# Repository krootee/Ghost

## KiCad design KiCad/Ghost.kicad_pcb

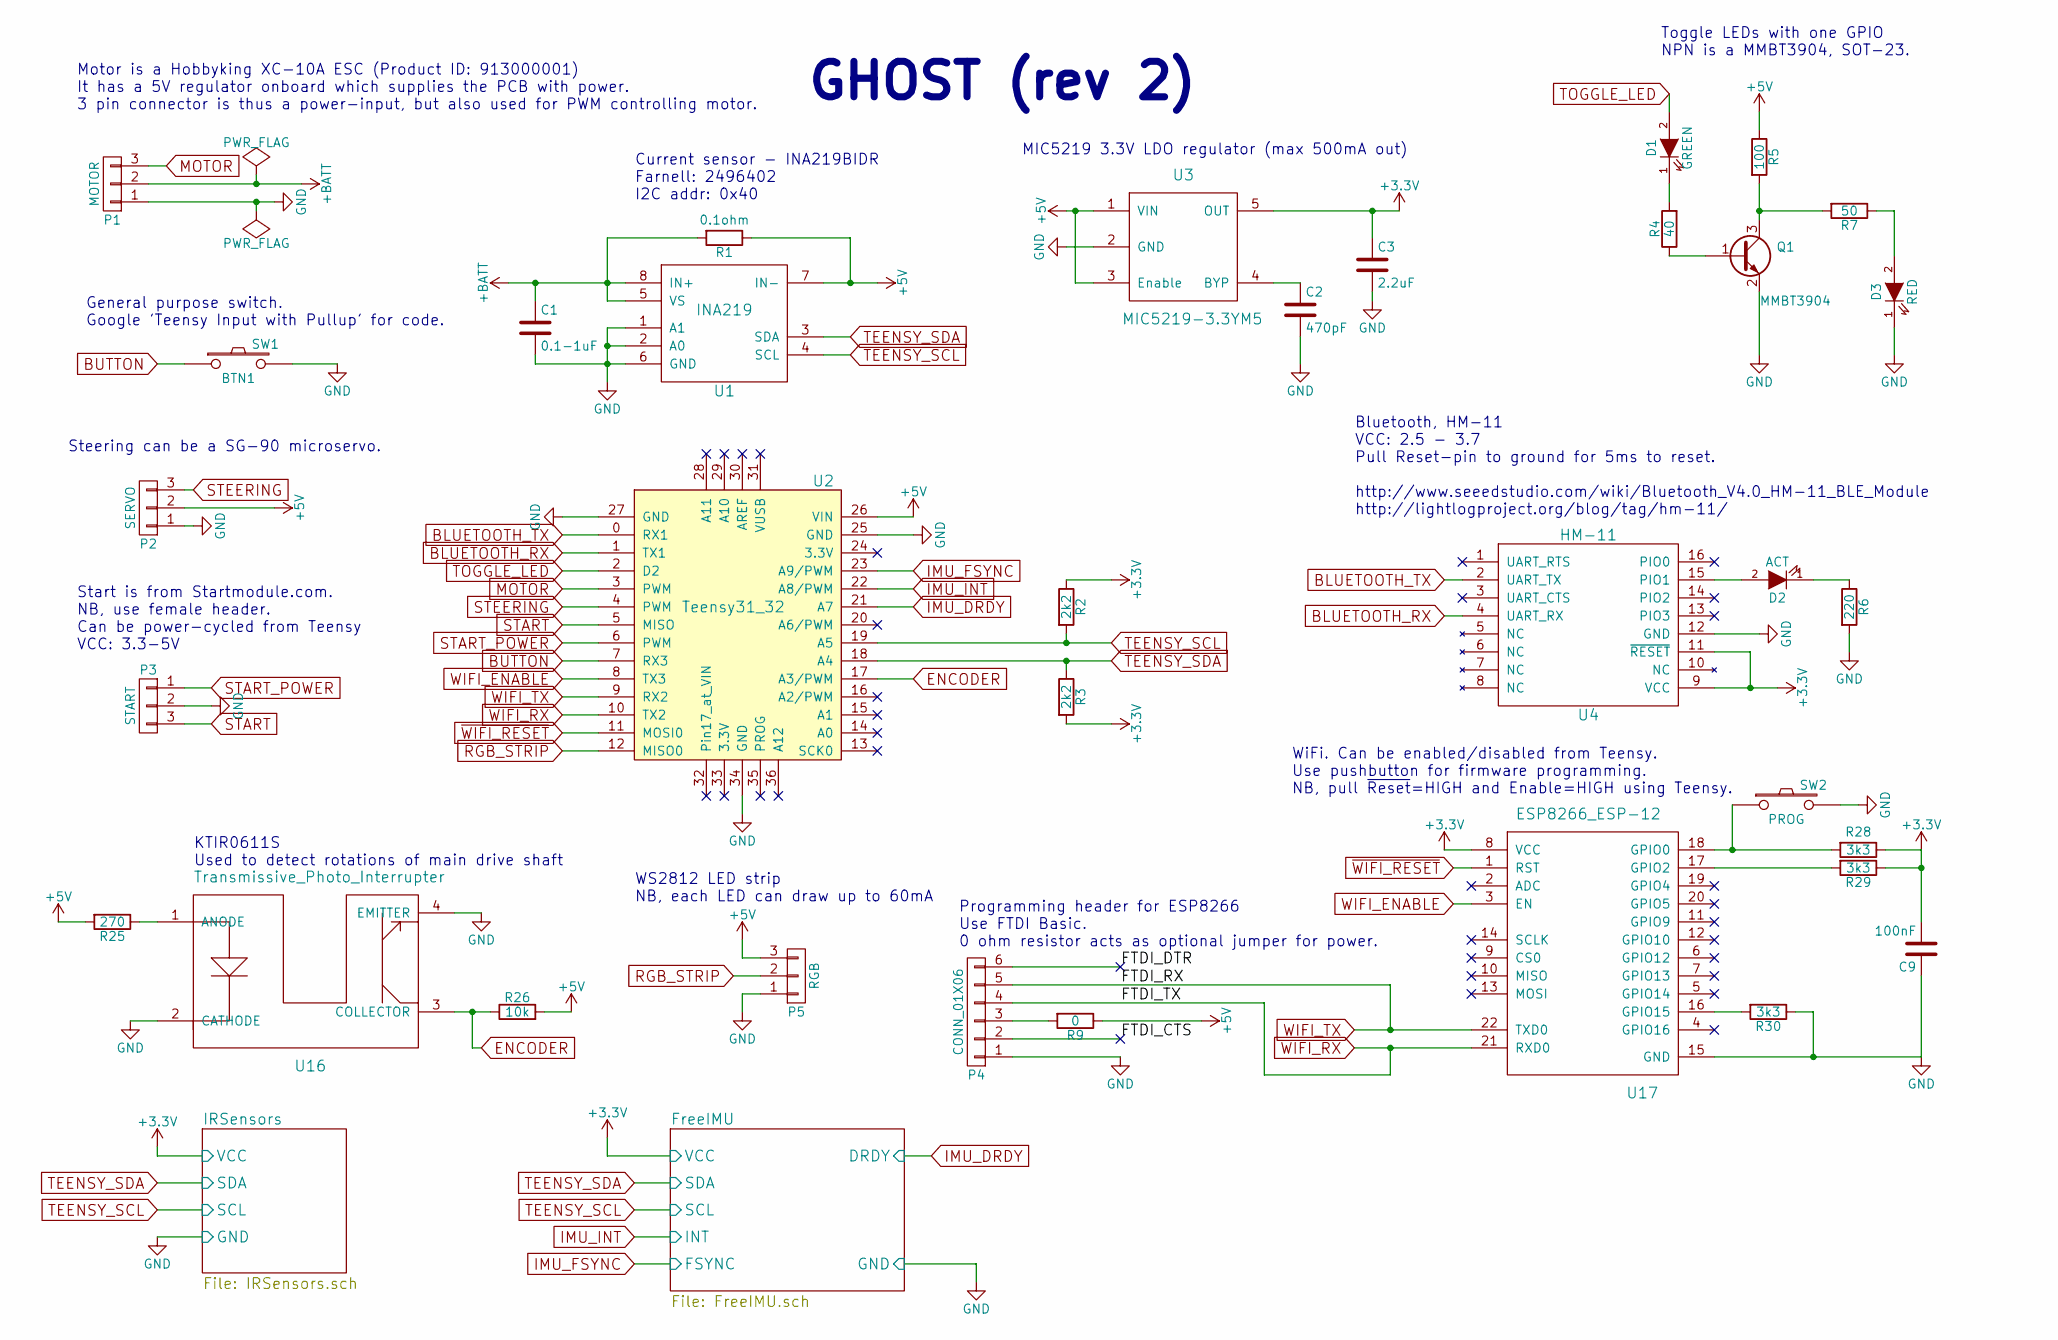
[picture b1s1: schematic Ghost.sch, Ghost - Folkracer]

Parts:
C1: 0.1-1uF; C_0603
C2: 470pF; C_0603
C3: 2.2uF; C_0603
C9: 100nF; C_0603
D1: GREEN; LED_0603
D2: ACT; LED_0603
D3: RED; LED_0603
P1: MOTOR; Pin_Header_Straight_1x03
P2: SERVO; Pin_Header_Straight_1x03
P3: START; Pin_Header_Straight_1x03
P4: CONN_01X06; Pin_Header_Straight_1x06
P5: RGB; Pin_Header_Straight_1x03
Q1: MMBT3904; SOT-23
R1: 0.1ohm; R_0603
R2, R3: 2k2; R_0603
R4: 40; R_0603
R5: 100; R_0603
R6: 220; R_0603
R7: 50; R_0603
R9: 0; R_0603
R25: 270; R_0603
R26: 10k; R_0603
R28, R29, R30: 3k3; R_0603
SW1: BTN1; SW_SPST_SKQG
SW2: PROG; SW_SPST_SKQG
U1: INA219; SOIC-8_3.9x4.9mm_Pitch1.27mm
U2: Teensy31_32; Teensy-3.1_3.2
U3: MIC5219-3.3YM5; SOT-23-5
U4: HM-11
U16: Transmissive_Photo_Interrupter; Pin_Header_Straight_1x04
U17: ESP8266_ESP-12; ESP8266_ESP_12E

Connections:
+3V3: C3.1, C9.2, R2.1, R3.2, R28.1, R29.1, U3.5 (OUT), U4.9 (VCC), U4.11 (~RESET), U17.8 (VCC); also elsewhere on the board
+5V: P2.2, P5.3, R1.1, R5.1, R9.1, R25.2, R26.2, U1.7 (IN-), U2.26 (VIN), U3.1 (VIN), U3.3 (Enable)
+BATT: C1.1, P1.2, R1.2, U1.5 (VS), U1.8 (IN+)
BLUETOOTH_RX: U2.1 (TX1), U4.4 (UART_RX)
BLUETOOTH_TX: U2.0 (RX1), U4.2 (UART_TX)
BUTTON: SW1.1, U2.7 (RX3)
ENCODER: R26.1, U2.17 (A3/PWM), U16.3 (COLLECTOR)
GND: C1.2, C2.2, C3.2, C9.1, D3.1 (K), P1.1, P2.1, P3.2, P4.1, P5.1, Q1.2 (E), R6.2, R30.1, SW1.2, SW2.2, U1.1 (A1), U1.2 (A0), U1.6 (GND), U2.25 (GND), U2.27 (GND), U2.34 (GND), U3.2 (GND), U4.12 (GND), U16.2 (CATHODE), U16.4 (EMITTER), U17.15 (GND); also elsewhere on the board
IMU_DRDY: U2.21 (A7); also elsewhere on the board
IMU_FSYNC: U2.23 (A9/PWM); also elsewhere on the board
IMU_INT: U2.22 (A8/PWM); also elsewhere on the board
MOTOR: P1.3, U2.3 (PWM)
unnamed: C2.1, U3.4 (BYP)
unnamed: D1.1 (K), R4.2
unnamed: D2.1 (K), R6.1
unnamed: D2.2 (A), U4.15 (PIO1)
unnamed: D3.2 (A), R7.1
unnamed: P4.3, R9.2
unnamed: Q1.1 (B), R4.1
unnamed: Q1.3 (C), R5.2, R7.2
unnamed: R25.1, U16.1 (ANODE)
unnamed: R28.2, SW2.1, U17.18 (GPIO0)
unnamed: R29.2, U17.17 (GPIO2)
unnamed: R30.2, U17.16 (GPIO15)
RGB_STRIP: P5.2, U2.12 (MISO0)
START: P3.3, U2.5 (MISO)
START_POWER: P3.1, U2.6 (PWM)
STEERING: P2.3, U2.4 (PWM)
TEENSY_SCL: R2.2, U1.4 (SCL), U2.19 (A5); also elsewhere on the board
TEENSY_SDA: R3.1, U1.3 (SDA), U2.18 (A4); also elsewhere on the board
TOGGLE_LED: D1.2 (A), U2.2 (D2)
WIFI_ENABLE: U2.8 (TX3), U17.3 (EN)
WIFI_RX: P4.4, U2.10 (TX2), U17.21 (RXD0)
WIFI_TX: P4.5, U2.9 (RX2), U17.22 (TXD0)
~WIFI_RESET: U2.11 (MOSI0), U17.1 (RST)

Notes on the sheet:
GHOST (rev 2)
Current sensor - INA219BIDR Farnell: 2496402 I2C addr: 0x40
MIC5219 3.3V LDO regulator (max 500mA out)
Toggle LEDs with one GPIO NPN is a MMBT3904, SOT-23.
Motor is a Hobbyking XC-10A ESC (Product ID: 913000001) It has a 5V regulator onboard which supplies the PCB with power. 3 pin connector is thus a power-input, but also used for PWM controlling motor.
Steering can be a SG-90 microservo.
Start is from Startmodule.com. NB, use female header. Can be power-cycled from Teensy VCC: 3.3-5V
General purpose switch. Google 'Teensy Input with Pullup' for code.
WS2812 LED strip NB, each LED can draw up to 60mA
Bluetooth, HM-11 VCC: 2.5 - 3.7 Pull Reset-pin to ground for 5ms to reset. http://www.seeedstudio.com/wiki/Bluetooth_V4.0_HM-11_BLE_Module http://lightlogproject.org/blog/tag/hm-11/
KTIR0611S Used to detect rotations of main drive shaft
WiFi. Can be enabled/disabled from Teensy. Use pushbutton for firmware programming. NB, pull ~Reset~=HIGH and Enable=HIGH using Teensy.
Programming header for ESP8266 Use FTDI Basic. 0 ohm resistor acts as optional jumper for power.

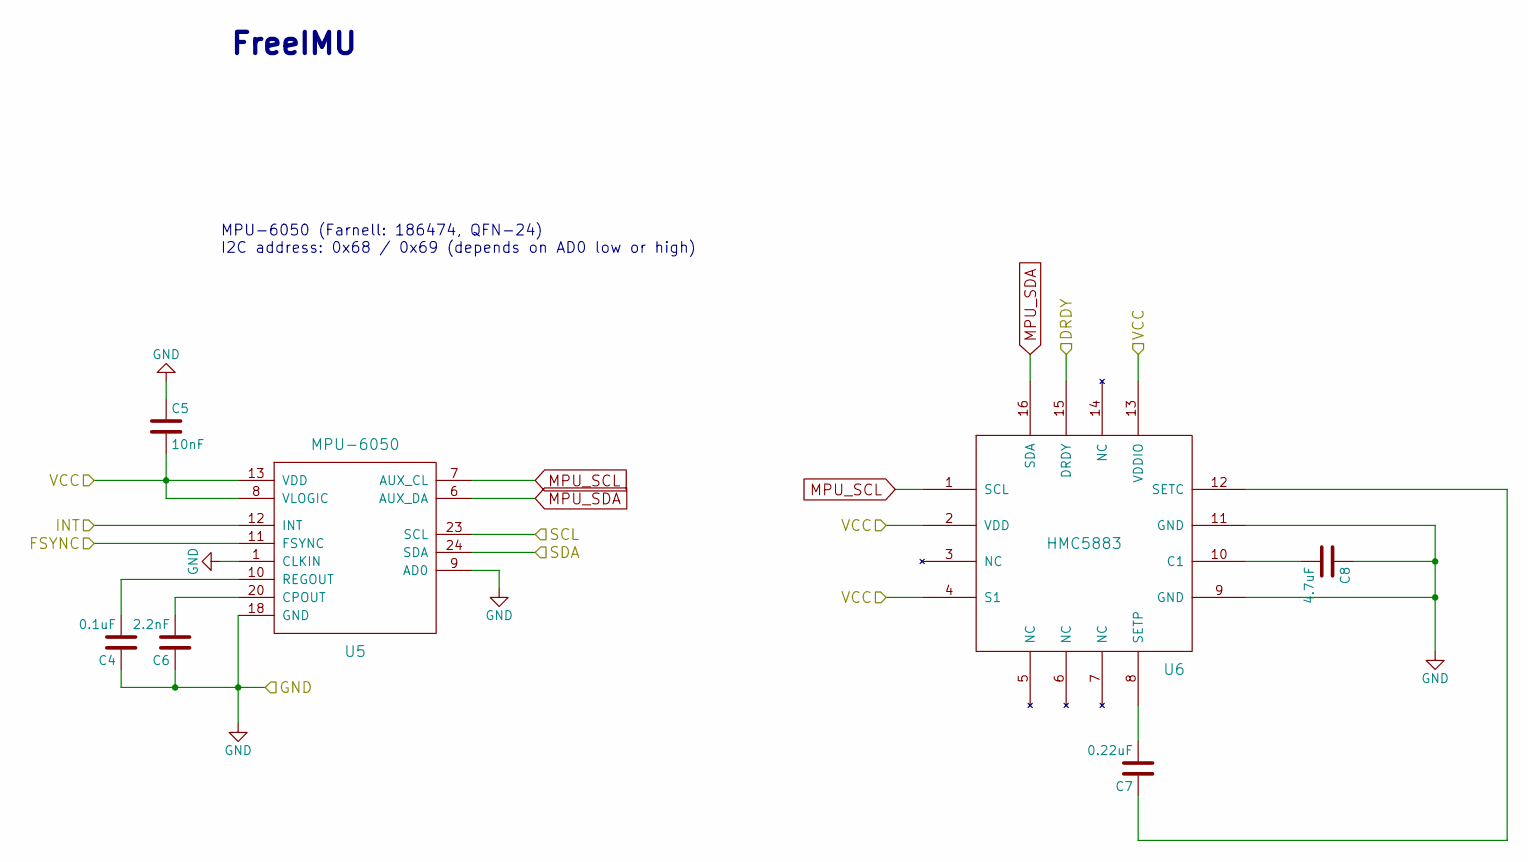
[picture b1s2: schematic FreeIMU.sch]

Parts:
C4: 0.1uF; C_0603
C5: 10nF; C_0603
C6: 2.2nF; C_0603
C7: 0.22uF; C_0603
C8: 4.7uF; C_0603
U5: MPU-6050; QFN-24-1EP_4x4mm_Pitch0.5mm
U6: HMC5883; QFN-16-1EP_3x3mm_Pitch0.5mm

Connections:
+3V3: C5.2, U5.8 (VLOGIC), U5.13 (VDD), U6.2 (VDD), U6.4 (S1), U6.13 (VDDIO); also elsewhere on the board
GND: C4.1, C5.1, C6.1, C8.1, U5.1 (CLKIN), U5.9 (AD0), U5.18 (GND), U6.9 (GND), U6.11 (GND); also elsewhere on the board
IMU_DRDY: U6.15 (DRDY); also elsewhere on the board
IMU_FSYNC: U5.11 (FSYNC); also elsewhere on the board
IMU_INT: U5.12 (INT); also elsewhere on the board
MPU_SCL: U5.7 (AUX_CL), U6.1 (SCL)
MPU_SDA: U5.6 (AUX_DA), U6.16 (SDA)
unnamed: C4.2, U5.10 (REGOUT)
unnamed: C6.2, U5.20 (CPOUT)
unnamed: C7.1, U6.12 (SETC)
unnamed: C7.2, U6.8 (SETP)
unnamed: C8.2, U6.10 (C1)
TEENSY_SCL: U5.23 (SCL); also elsewhere on the board
TEENSY_SDA: U5.24 (SDA); also elsewhere on the board

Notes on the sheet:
MPU-6050 (Farnell: 186474, QFN-24) I2C address: 0x68 / 0x69 (depends on AD0 low or high)
FreeIMU

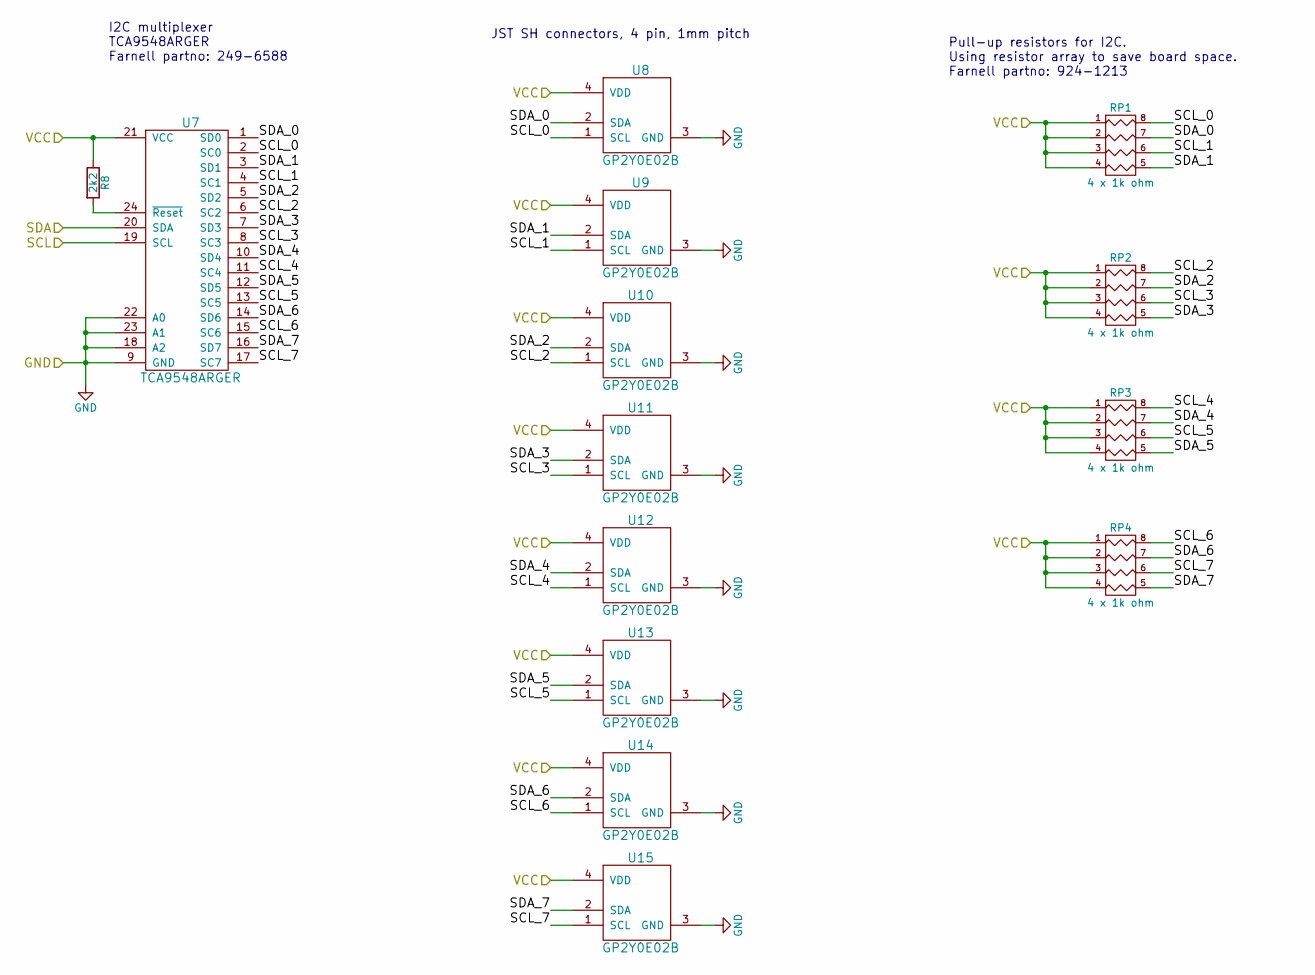
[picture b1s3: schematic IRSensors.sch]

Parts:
R8: 2k2; R_0603
RP1, RP2, RP3, RP4: 4 x 1k ohm; R_Array_Convex_4x0603
U7: TCA9548ARGER; QFN-24-1EP_4x4mm_Pitch0.5mm
U8, U9, U10, U11, U12, U13, U14, U15: GP2Y0E02B; JST_SH_BM04B-SRSS-TB_04x1.00mm_Straight

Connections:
+3V3: R8.1, RP1.1, RP1.2, RP1.3, RP1.4, RP2.1, RP2.2, RP2.3, RP2.4, RP3.1, RP3.2, RP3.3, RP3.4, RP4.1, RP4.2, RP4.3, RP4.4, U7.21 (VCC), U8.4 (VDD), U9.4 (VDD), U10.4 (VDD), U11.4 (VDD), U12.4 (VDD), U13.4 (VDD), U14.4 (VDD), U15.4 (VDD); also elsewhere on the board
/IRSensors/SCL_0: RP1.8 (R1), U7.2 (SC0), U8.1 (SCL)
/IRSensors/SCL_1: RP1.6 (R3), U7.4 (SC1), U9.1 (SCL)
/IRSensors/SCL_2: RP2.8 (R1), U7.6 (SC2), U10.1 (SCL)
/IRSensors/SCL_3: RP2.6 (R3), U7.8 (SC3), U11.1 (SCL)
/IRSensors/SCL_4: RP3.8 (R1), U7.11 (SC4), U12.1 (SCL)
/IRSensors/SCL_5: RP3.6 (R3), U7.13 (SC5), U13.1 (SCL)
/IRSensors/SCL_6: RP4.8 (R1), U7.15 (SC6), U14.1 (SCL)
/IRSensors/SCL_7: RP4.6 (R3), U7.17 (SC7), U15.1 (SCL)
/IRSensors/SDA_0: RP1.7 (R2), U7.1 (SD0), U8.2 (SDA)
/IRSensors/SDA_1: RP1.5 (R4), U7.3 (SD1), U9.2 (SDA)
/IRSensors/SDA_2: RP2.7 (R2), U7.5 (SD2), U10.2 (SDA)
/IRSensors/SDA_3: RP2.5 (R4), U7.7 (SD3), U11.2 (SDA)
/IRSensors/SDA_4: RP3.7 (R2), U7.10 (SD4), U12.2 (SDA)
/IRSensors/SDA_5: RP3.5 (R4), U7.12 (SD5), U13.2 (SDA)
/IRSensors/SDA_6: RP4.7 (R2), U7.14 (SD6), U14.2 (SDA)
/IRSensors/SDA_7: RP4.5 (R4), U7.16 (SD7), U15.2 (SDA)
GND: U7.9 (GND), U7.18 (A2), U7.22 (A0), U7.23 (A1), U8.3 (GND), U9.3 (GND), U10.3 (GND), U11.3 (GND), U12.3 (GND), U13.3 (GND), U14.3 (GND), U15.3 (GND); also elsewhere on the board
unnamed: R8.2, U7.24 (~Reset)
TEENSY_SCL: U7.19 (SCL); also elsewhere on the board
TEENSY_SDA: U7.20 (SDA); also elsewhere on the board

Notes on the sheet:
JST SH connectors, 4 pin, 1mm pitch
Pull-up resistors for I2C. Using resistor array to save board space. Farnell partno: 924-1213
I2C multiplexer TCA9548ARGER Farnell partno: 249-6588

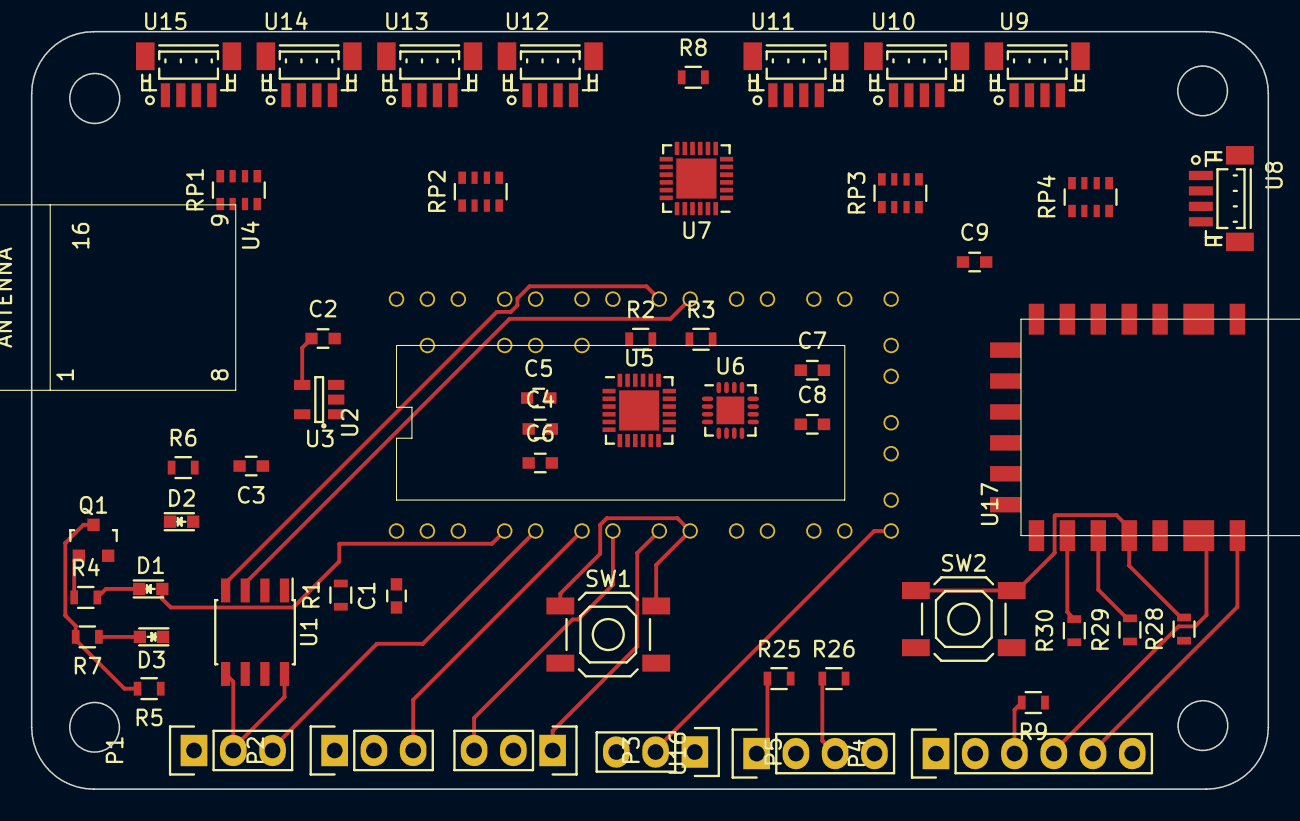
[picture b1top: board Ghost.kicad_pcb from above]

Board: 2 copper layers, 80.0 x 49.0 mm, 55 parts (0 on the bottom side), 59 nets.

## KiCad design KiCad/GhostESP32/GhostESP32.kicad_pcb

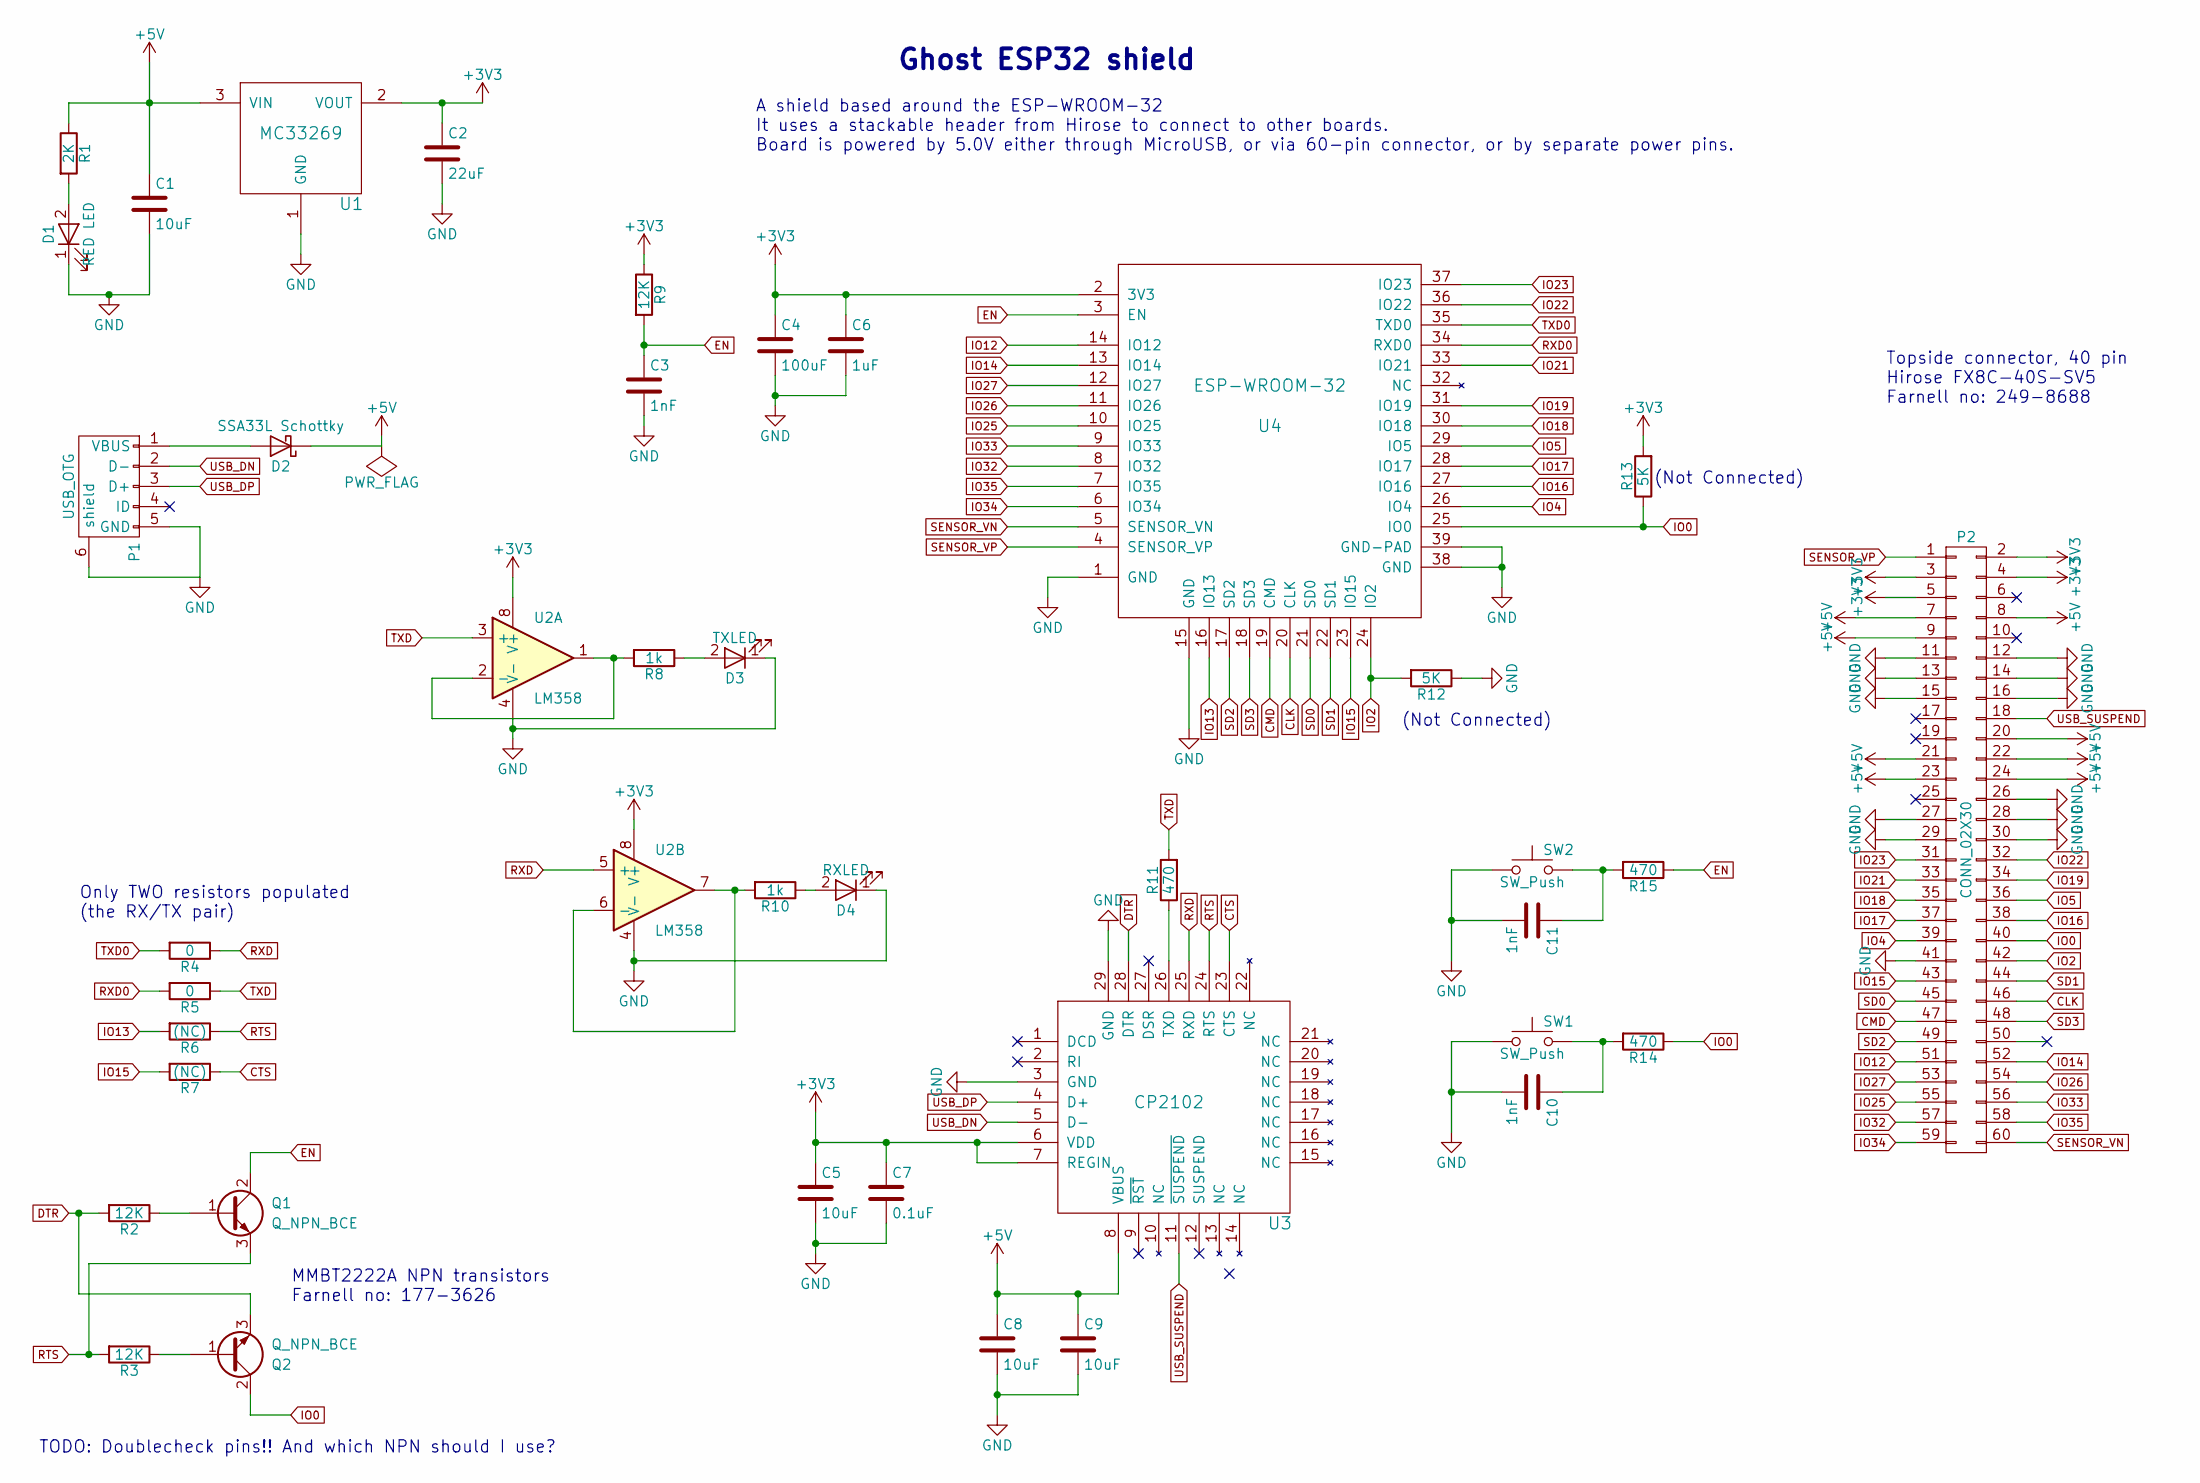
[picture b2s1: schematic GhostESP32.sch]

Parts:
C1, C5, C8, C9: 10uF; C_0603
C2: 22uF; C_0603
C3, C10, C11: 1nF; C_0603
C4: 100uF; C_0603
C6: 1uF; C_0603
C7: 0.1uF; C_0603
D1: RED LED; LED_0603
D2: SSA33L Schottky; D_SMA_Standard
D3: TXLED; LED_0603
D4: RXLED; LED_0603
P1: USB_OTG; USB_Micro-B
P2: CONN_02X30; hrs-fx8c-60p-sv
Q1, Q2: Q_NPN_BCE; SOT-23
R1: 2K; R_0603
R2, R3, R9: 12K; R_0603
R4, R5: 0; R_0603
R6, R7: (NC); R_0603
R8, R10: 1k; R_0603
R11, R14, R15: 470; R_0603
R12, R13: 5K; R_0603
SW1, SW2: SW_Push; SW_SPST_EVQP2
U1: MC33269; TO-252-2Lead
U2: LM358; SOIC-8_3.9x4.9mm_Pitch1.27mm
U3: CP2102; QFN-28-1EP_5x5mm_Pitch0.5mm
U4: ESP-WROOM-32; ESP32-WROOM

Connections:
+3V3: C2.1, C4.1, C5.1, C6.1, C7.1, P2.2, P2.3, P2.4, P2.5, R9.1, R13.2, U1.2 (VOUT), U2.8 (V+), U3.6 (VDD), U3.7 (REGIN), U4.2 (3V3)
+5V: C1.1, C8.1, C9.1, D2.1 (K), P2.7, P2.8, P2.9, P2.20, P2.21, P2.22, P2.23, P2.24, R1.1, U1.3 (VIN), U3.8 (VBUS)
CLK: P2.46, U4.20 (CLK)
CMD: P2.47, U4.19 (CMD)
CTS: R7.1, U3.23 (CTS)
DTR: Q2.3 (E), R2.2, U3.28 (DTR)
EN: C3.1, Q1.2 (C), R9.2, R15.1, U4.3 (EN)
GND: C1.2, C2.2, C3.2, C4.2, C5.2, C6.2, C7.2, C8.2, C9.2, C10.2, C11.2, D1.1 (K), D3.1 (K), D4.1 (K), P1.5 (GND), P1.6 (shield), P2.11, P2.12, P2.13, P2.14, P2.15, P2.16, P2.26, P2.27, P2.28, P2.29, P2.30, P2.41, R12.1, SW1.1, SW2.1, U1.1 (GND), U2.4 (V-), U3.3 (GND), U3.29 (GND), U4.1 (GND), U4.15 (GND), U4.38 (GND), U4.39 (GND-PAD); also elsewhere on the board
IO0: P2.40, Q2.2 (C), R13.1, R14.1, U4.25 (IO0)
IO2: P2.42, R12.2, U4.24 (IO2)
IO4: P2.39, U4.26 (IO4)
IO5: P2.36, U4.29 (IO5)
IO12: P2.51, U4.14 (IO12)
IO13: R6.2, U4.16 (IO13)
IO14: P2.52, U4.13 (IO14)
IO15: P2.43, R7.2, U4.23 (IO15)
IO16: P2.38, U4.27 (IO16)
IO17: P2.37, U4.28 (IO17)
IO18: P2.35, U4.30 (IO18)
IO19: P2.34, U4.31 (IO19)
IO21: P2.33, U4.33 (IO21)
IO22: P2.32, U4.36 (IO22)
IO23: P2.31, U4.37 (IO23); also elsewhere on the board
IO25: P2.55, U4.10 (IO25)
IO26: P2.54, U4.11 (IO26)
IO27: P2.53, U4.12 (IO27)
IO32: P2.57, U4.8 (IO32)
IO33: P2.56, U4.9 (IO33)
IO34: P2.59, U4.6 (IO34)
IO35: P2.58, U4.7 (IO35)
unnamed: C10.1, R14.2, SW1.2
unnamed: C11.1, R15.2, SW2.2
unnamed: D1.2 (A), R1.2
unnamed: D2.2 (A), P1.1 (VBUS)
unnamed: D3.2 (A), R8.1
unnamed: D4.2 (A), R10.1
unnamed: Q1.1 (B), R2.1
unnamed: Q2.1 (B), R3.1
unnamed: R8.2, U2.1, U2.2 (-)
unnamed: R10.2, U2.6 (-), U2.7
unnamed: R11.1, U3.26 (TXD)
RTS: Q1.3 (E), R3.2, R6.1, U3.24 (RTS)
RXD: R4.1, U2.5 (+), U3.25 (RXD)
RXD0: R5.2, U4.34 (RXD0)
SD0: P2.45, U4.21 (SD0)
SD1: P2.44, U4.22 (SD1)
SD2: P2.49, U4.17 (SD2)
SD3: P2.48, U4.18 (SD3)
SENSOR_VN: P2.60, U4.5 (SENSOR_VN)
SENSOR_VP: P2.1, U4.4 (SENSOR_VP)
TXD: R5.1, R11.2, U2.3 (+)
TXD0: R4.2, U4.35 (TXD0)
USB_DN: P1.2 (D-), U3.5 (D-)
USB_DP: P1.3 (D+), U3.4 (D+)
USB_SUSPEND: P2.18, U3.11 (~SUSPEND)

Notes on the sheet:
Ghost ESP32 shield
A shield based around the ESP-WROOM-32 It uses a stackable header from Hirose to connect to other boards. Board is powered by 5.0V either through MicroUSB, or via 60-pin connector, or by separate power pins.
Topside connector, 40 pin Hirose FX8C-40S-SV5 Farnell no: 249-8688
TODO: Doublecheck pins!! And which NPN should I use?
Only TWO resistors populated (the RX/TX pair)
(Not Connected)
MMBT2222A NPN transistors Farnell no: 177-3626

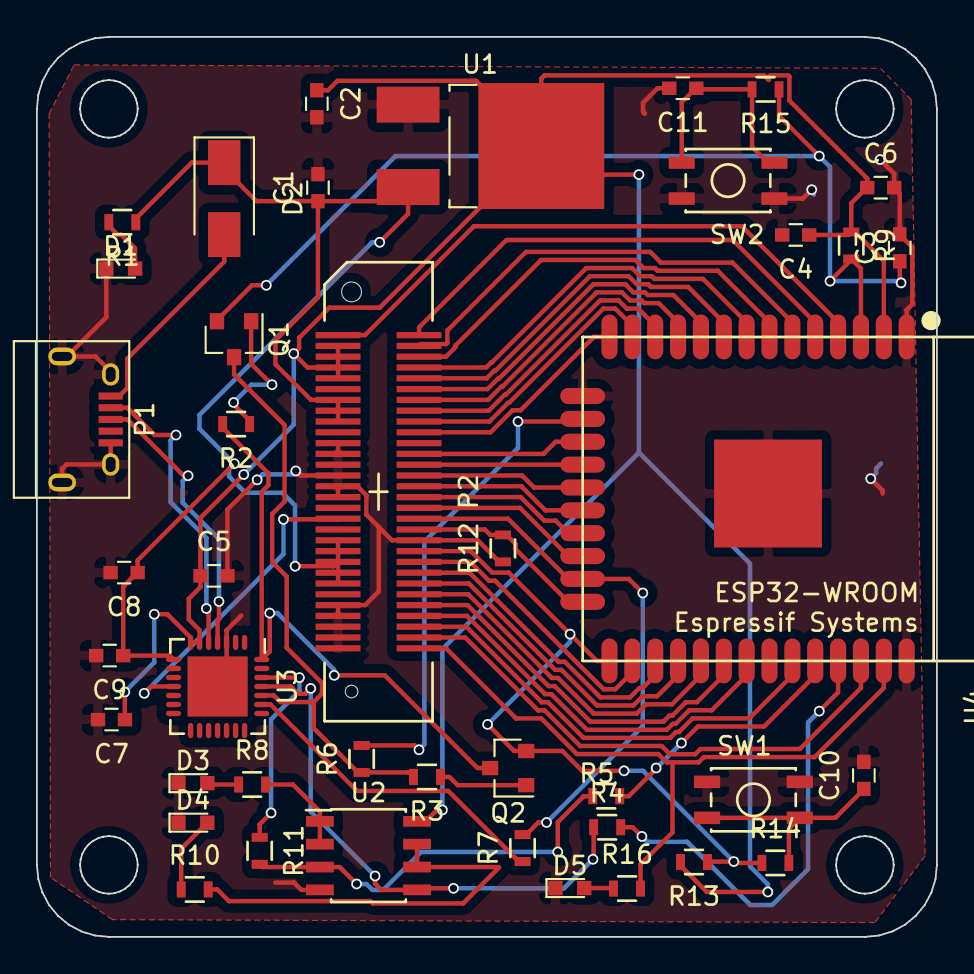
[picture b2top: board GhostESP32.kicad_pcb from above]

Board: 2 copper layers, 50.0 x 50.0 mm, 42 parts (0 on the bottom side), 56 nets.

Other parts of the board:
D5: LED; LED_0603
R16: 330; R_0603

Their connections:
GND: D5.1; also elsewhere on the board
IO23: R16.2; also elsewhere on the board
unnamed: D5.2, R16.1

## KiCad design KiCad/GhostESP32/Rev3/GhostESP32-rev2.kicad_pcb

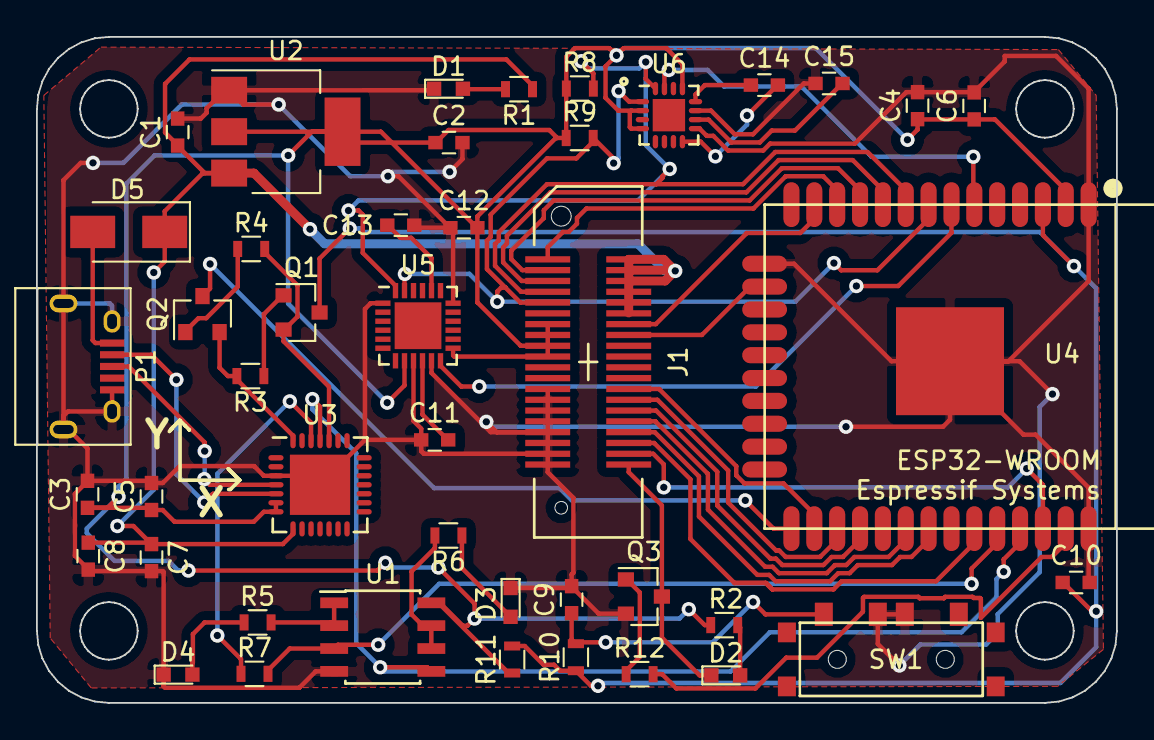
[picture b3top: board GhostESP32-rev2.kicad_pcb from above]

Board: 2 copper layers, 60.0 x 37.0 mm, 44 parts (0 on the bottom side), 46 nets.

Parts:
C1, C2, C3, C7: 10uF; C_0603
C4: 100uF; C_0603
C5, C8, C11: 0.1uF; C_0603
C6: 1uF; C_0603
C9, C10: 1nF; C_0603
C12: 10nF; C_0603
C13: 2.2nF; C_0603
C14: 0.22uF; C_0603
C15: 4.7uF; C_0603
D1: RED LED; LED_0603
D2: LED; LED_0603
D3: RXLED; LED_0603
D4: TXLED; LED_0603
D5: SSA33L Schottky; D_SMA_Standard
J1: CONN_02X20; hrs-fx8c-40p-sv
P1: USB_OTG; USB_Micro-B
Q1, Q2, Q3: Q_NPN_BEC; SOT-23
R1: 2K; R_0603
R2: 390; R_0603
R3, R4, R11: 12K; R_0603
R5, R6: 1k; R_0603
R7, R10: 470; R_0603
R8, R9: 2k2; R_0603
R12: 10k; R_0603
SW1: SW_SPDT; SlideSwitchSpringReturn
U1: LM358; SOIC-8_3.9x4.9mm_Pitch1.27mm
U2: NCP1117ST33T3G; SOT-223-3Lead_TabPin2
U3: CP2102; QFN-28-1EP_5x5mm_Pitch0.5mm
U4: ESP-WROOM-32; ESP32-WROOM
U5: MPU-6050; QFN-24-1EP_4x4mm_Pitch0.5mm
U6: HMC5883; QFN-16-1EP_3x3mm_Pitch0.5mm

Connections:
+3V3: C2.1, C3.1, C4.1, C5.1, C6.1, C12.2, J1.7, J1.8, J1.9, J1.10, R2.2, R8.1, R9.1, R11.1, U1.8, U2.2, U3.6, U3.7, U4.2, U5.8, U5.13, U6.2, U6.4, U6.13
+5V: C1.1, C7.1, C8.1, D5.1, J1.35, J1.36, J1.37, J1.38, J1.39, J1.40, R1.1, U2.3, U3.8
DTR: Q2.2, R3.2, U3.28
EN: C10.1, Q1.3, R10.1, R11.2, U4.3
GND: C1.2, C2.2, C3.2, C4.2, C5.2, C6.2, C7.2, C8.2, C9.2, C10.2, C11.1, C12.1, C13.1, C15.1, D1.1, D3.1, D4.1, J1.13, J1.14, J1.15, J1.16, J1.17, J1.18, J1.19, J1.20, P1.5, P1.6, Q3.2, SW1.2, U1.4, U2.1, U3.3, U3.29, U4.1, U4.15, U4.38, U4.39, U5.1, U5.9, U5.11, U5.18, U6.9, U6.11
IO0: Q2.3, U4.25
IO4: J1.28, U4.26
IO13: J1.33, U4.16
IO14: J1.34, U4.13
IO16: J1.27, U4.27
IO17: J1.26, U4.28
IO18: J1.25, U4.30
IO19: J1.24, U4.31
IO21: J1.23, U4.33
IO22: J1.22, U4.36
IO23: R12.2, U4.37
IO25: J1.3, U4.10
IO26: J1.2, U4.11
IO27: J1.1, U4.12
IO32: J1.5, R9.2, U4.8, U5.23, U6.1
IO33: J1.4, R8.2, U4.9, U5.24, U6.16
IO34: U4.6, U6.15
IO35: U4.7, U5.12
LED: D2.1, J1.21, Q3.3
unnamed: C9.1, R10.2, SW1.3
unnamed: C11.2, U5.10
unnamed: C13.2, U5.20
unnamed: C14.1, U6.12
unnamed: C14.2, U6.8
unnamed: C15.2, U6.10
unnamed: D1.2, R1.2
unnamed: D2.2, R2.1
unnamed: D3.2, R6.1
unnamed: D4.2, R5.1
unnamed: D5.2, P1.1
unnamed: Q1.1, R3.1
unnamed: Q2.1, R4.1
unnamed: Q3.1, R12.1
unnamed: R5.2, U1.1, U1.2
unnamed: R6.2, U1.6, U1.7
unnamed: R7.1, U3.26
RTS: Q1.2, R4.2, U3.24
RXD: U1.5, U3.25, U4.35
TXD: R7.2, U1.3, U4.34
USB_DN: P1.2, U3.5
USB_DP: P1.3, U3.4
